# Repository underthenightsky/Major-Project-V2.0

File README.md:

# Major Project V2.0
Research Paper to compare various models on a STM32F401CCU6 and design a PCB for pracitcal applications

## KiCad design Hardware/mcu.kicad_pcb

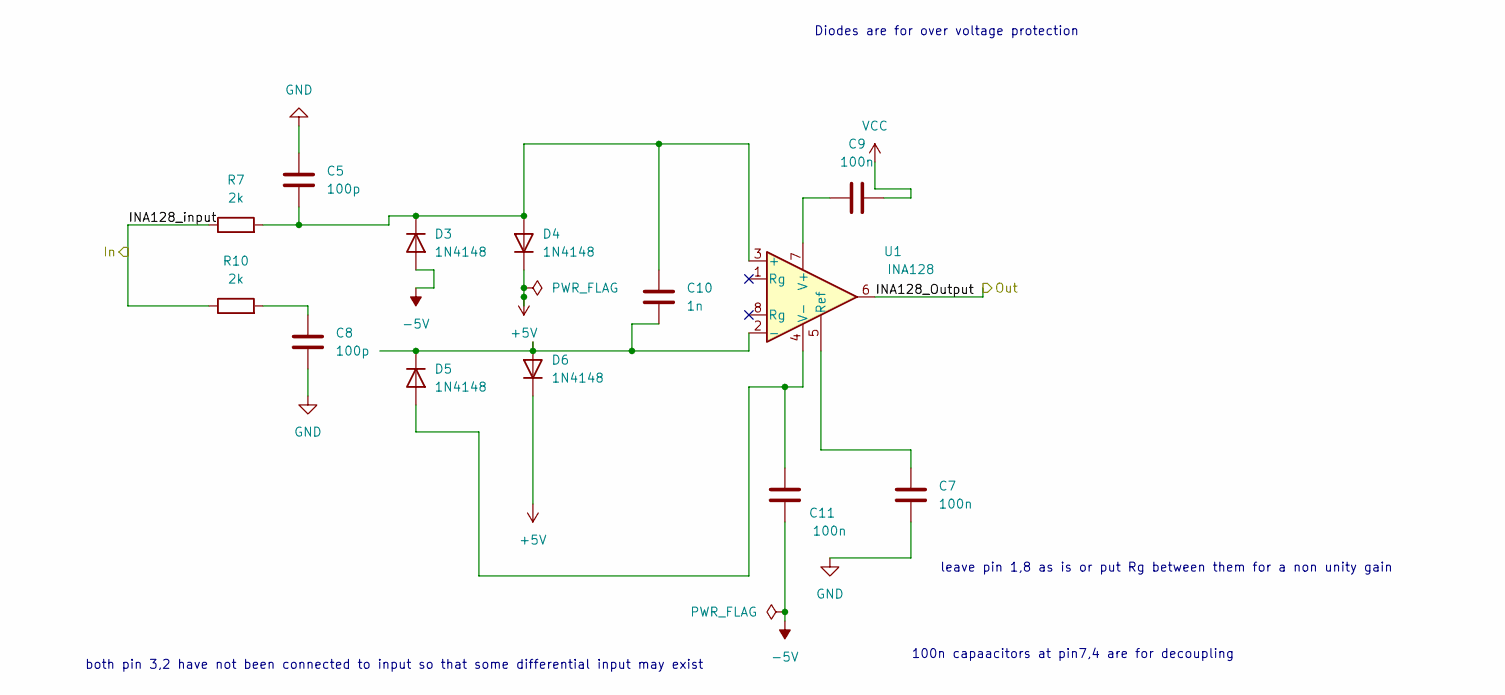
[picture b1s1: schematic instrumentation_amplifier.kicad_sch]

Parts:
C5, C8: 100p; C_0805_2012Metric
C7, C9, C11: 100n; C_01005_0402Metric
C10: 1n; C_0805_2012Metric
D3, D4, D5, D6: 1N4148; D_DO-35_SOD27_P7.62mm_Horizontal
R7, R10: 2k; R_0805_2012Metric
U1: INA128; SOIC-8_3.9x4.9mm_P1.27mm

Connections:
+5V: D4.1 (K), D6.1 (K); also elsewhere on the board
-5V: C11.2, D3.2 (A)
/instrumentation_amplifier/INA128_Output: U1.6; also elsewhere on the board
/instrumentation_amplifier/INA128_input: R7.1, R10.1; also elsewhere on the board
GND: C5.2, C7.2, C8.2; also elsewhere on the board
unnamed: C8.1, R10.2
unnamed: C5.1, C10.1, D3.1 (K), D4.2 (A), R7.2, U1.3 (+)
unnamed: C11.1, D5.2 (A), U1.4 (V-)
unnamed: C10.2, D5.1 (K), D6.2 (A), U1.2 (-)
unnamed: C7.1, U1.5 (Ref)
unnamed: C9.1, U1.7 (V+)
VCC: C9.2; also elsewhere on the board

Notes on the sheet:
100n capaacitors at pin7,4 are for decoupling
Diodes are for over voltage protection
both pin 3,2 have not been connected to input so that some differential input may exist
leave pin 1,8 as is or put Rg between them for a non unity gain

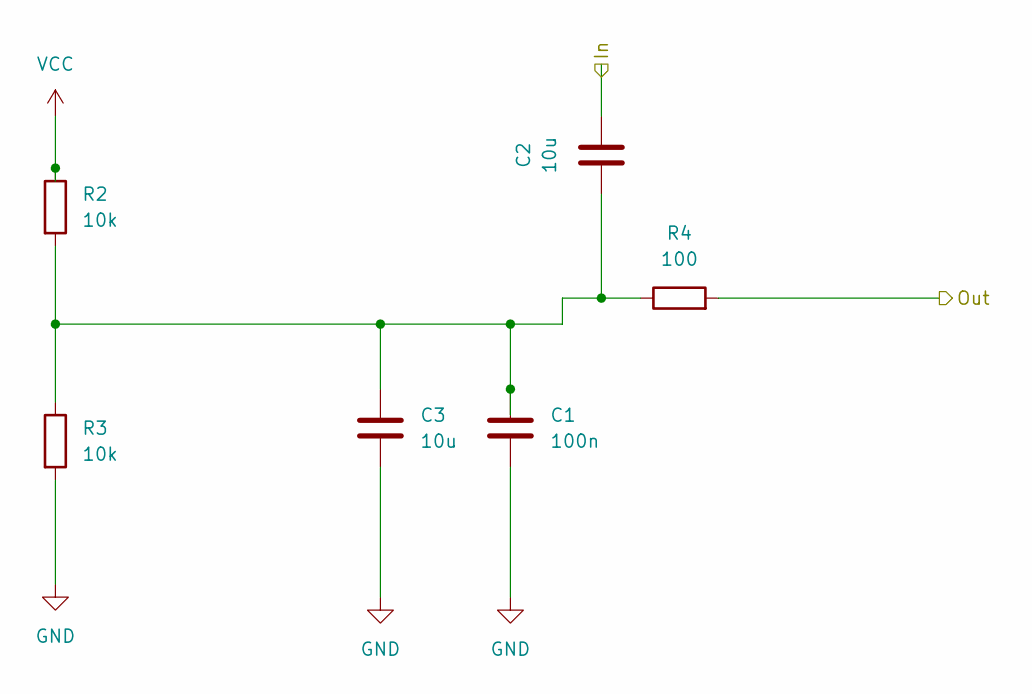
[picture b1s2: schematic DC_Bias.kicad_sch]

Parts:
C1: 100n; C_0805_2012Metric
C2: 10u; C_0805_2012Metric
C3: 10u; CP_Elec_6.3x5.4
R2, R3: 10k; R_0805_2012Metric
R4: 100; R_0805_2012Metric

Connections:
/DC_Bias/In: C2.2; also elsewhere on the board
/DC_Bias/Out: R4.2; also elsewhere on the board
GND: C1.2, C3.2, R3.2; also elsewhere on the board
unnamed: C1.1, C2.1, C3.1, R2.2, R3.1, R4.1
VCC: R2.1; also elsewhere on the board

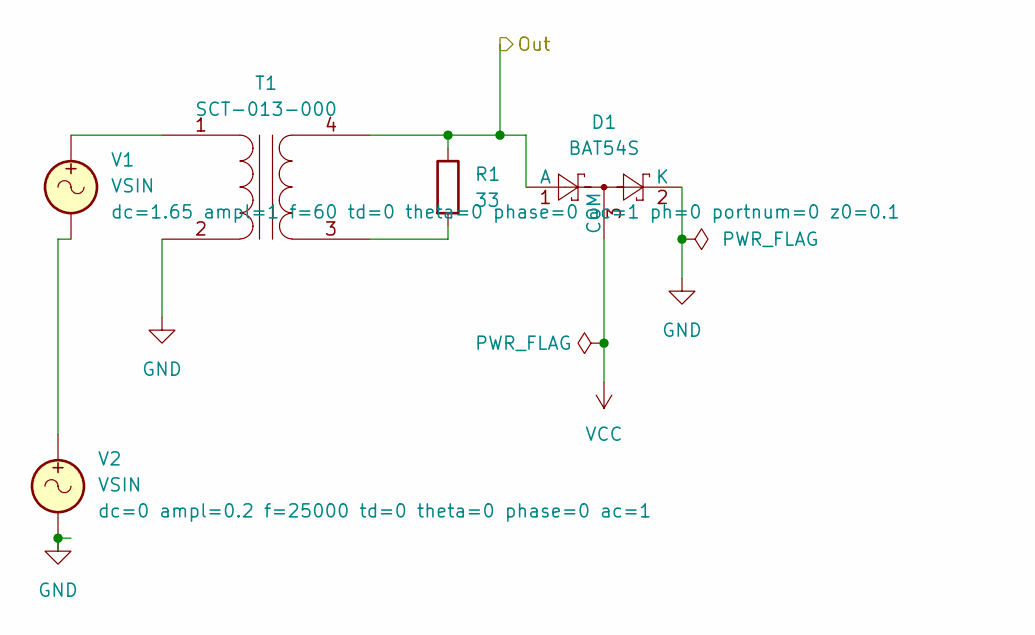
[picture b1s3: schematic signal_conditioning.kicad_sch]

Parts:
D1: BAT54S; SOT-23
R1: 33; R_0805_2012Metric
T1: SCT-013-000; TerminalBlock_MaiXu_MX126-5.0-04P_1x04_P5.00mm
V1, V2: VSIN

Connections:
/DC_Bias/In: D1.1 (A), R1.1, T1.4 (SB); also elsewhere on the board
GND: D1.2 (K), T1.2 (AB), V2.2; also elsewhere on the board
unnamed: T1.1 (AA), V1.1
unnamed: R1.2, T1.3 (SA)
unnamed: V1.2, V2.1
VCC: D1.3 (COM); also elsewhere on the board

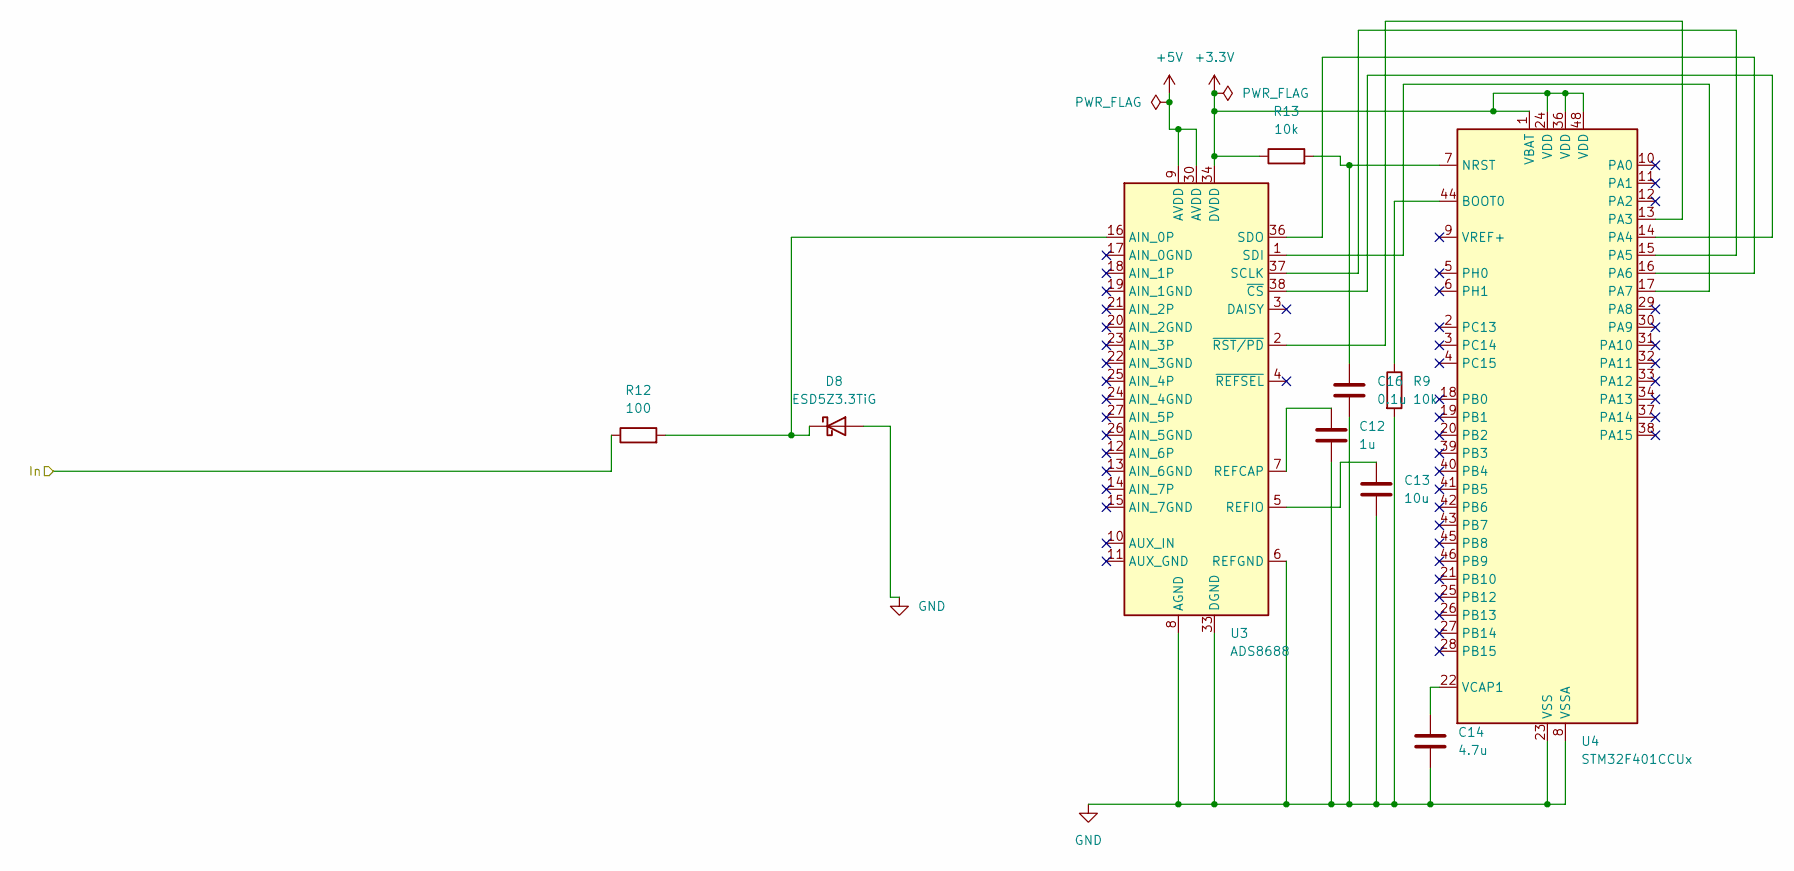
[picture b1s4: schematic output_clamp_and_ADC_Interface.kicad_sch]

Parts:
C12: 1u; C_0805_2012Metric
C13: 10u; C_0805_2012Metric
C14: 4.7u; C_0805_2012Metric
C16: 0.1u; C_0805_2012Metric
D8: ESD5Z3.3TiG; D_SOD-523
R9, R13: 10k; R_0805_2012Metric
R12: 100; R_0603_1608Metric
U3: ADS8688; TSSOP-38_4.4x9.7mm_P0.5mm
U4: STM32F401CCUx; QFN-48-1EP_7x7mm_P0.5mm_EP5.6x5.6mm

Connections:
+3.3V: R13.1, U3.34 (DVDD), U4.1 (VBAT), U4.24 (VDD), U4.36 (VDD), U4.48 (VDD)
+5V: U3.9 (AVDD), U3.30 (AVDD); also elsewhere on the board
/instrumentation_amplifier/INA128_Output: R12.1; also elsewhere on the board
GND: C12.2, C13.2, C14.2, C16.2, D8.2 (A), R9.2, U3.6 (REFGND), U3.8 (AGND), U3.28 (AGND), U3.29 (AGND), U3.31 (AGND), U3.32 (AGND), U3.33 (DGND), U4.8 (VSSA), U4.23 (VSS), U4.35 (VSS), U4.47 (VSS), U4.49 (VSS); also elsewhere on the board
unnamed: D8.1 (K), R12.2, U3.16 (AIN_0P)
unnamed: C12.1, U3.7 (REFCAP)
unnamed: C13.1, U3.5 (REFIO)
unnamed: U3.37 (SCLK), U4.15 (PA5)
unnamed: U3.1 (SDI), U4.17 (PA7)
unnamed: U3.36 (SDO), U4.16 (PA6)
unnamed: U3.38 (~CS), U4.14 (PA4)
unnamed: U3.2 (~RST/PD), U4.13 (PA3)
unnamed: R9.1, U4.44 (BOOT0)
unnamed: C16.1, R13.2, U4.7 (NRST)
unnamed: C14.1, U4.22 (VCAP1)

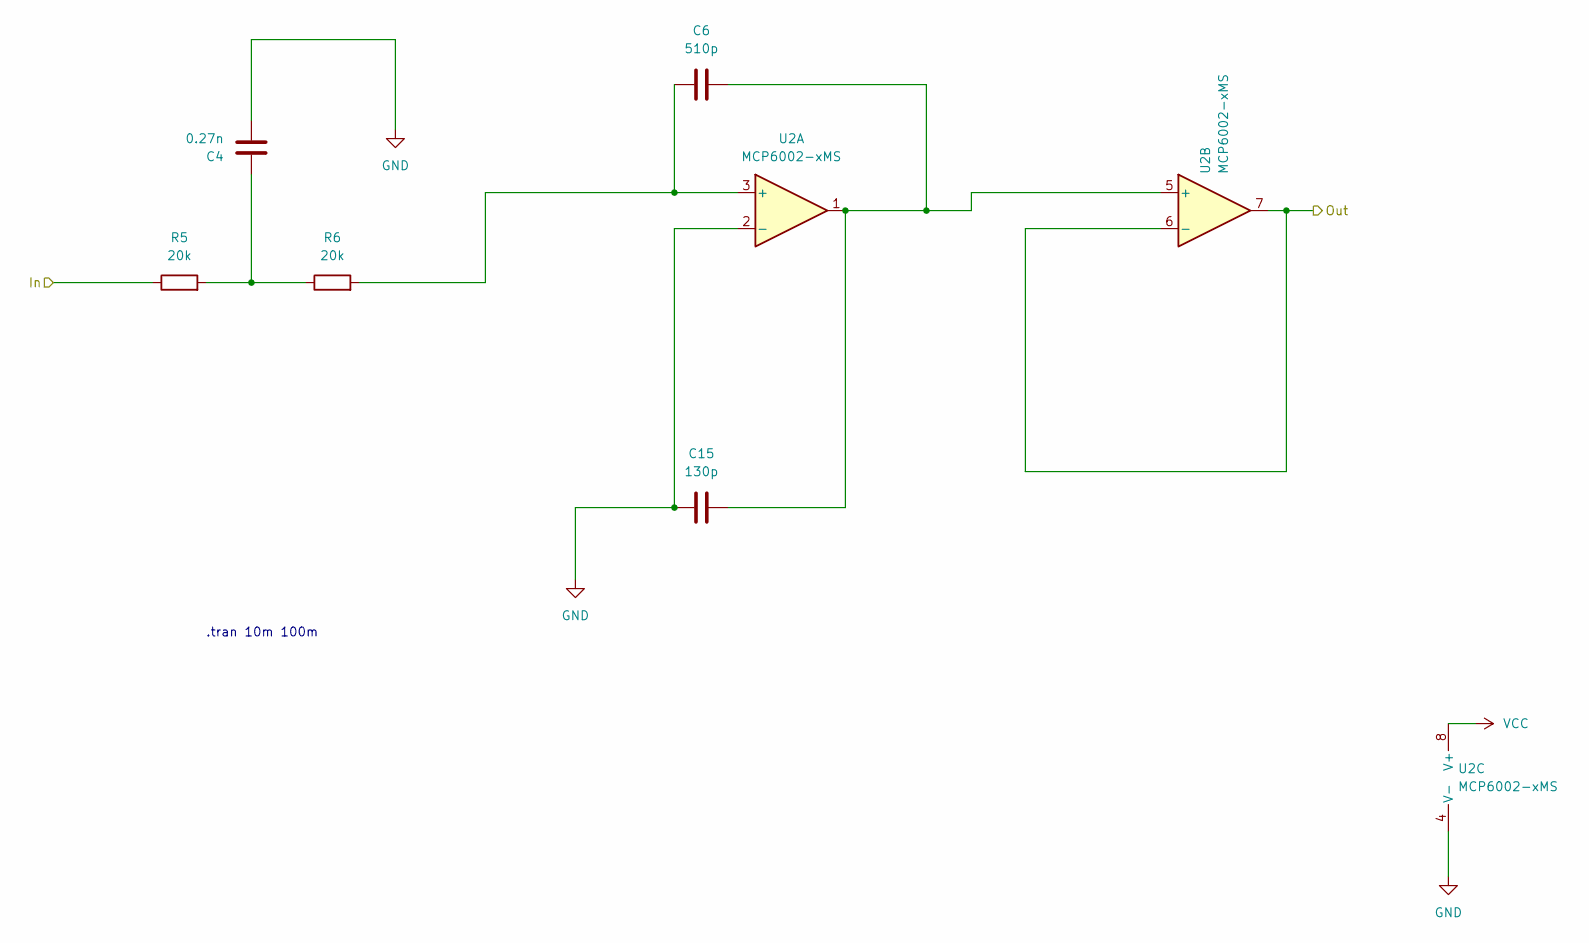
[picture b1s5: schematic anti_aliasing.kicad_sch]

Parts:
C4: 0.27n; C_0805_2012Metric
C6: 510p; C_0805_2012Metric
C15: 130p; C_0805_2012Metric
R5, R6: 20k; R_0805_2012Metric
U2: MCP6002-xMS; MSOP-8_3x3mm_P0.65mm

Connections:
/DC_Bias/Out: R5.1; also elsewhere on the board
/instrumentation_amplifier/INA128_input: U2.6 (-), U2.7; also elsewhere on the board
GND: C4.2, C15.1, U2.2 (-), U2.4 (V-); also elsewhere on the board
unnamed: C4.1, R5.2, R6.1
unnamed: C6.2, R6.2, U2.3 (+)
unnamed: C6.1, C15.2, U2.1, U2.5 (+)
VCC: U2.8 (V+); also elsewhere on the board

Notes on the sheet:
.tran 10m 100m

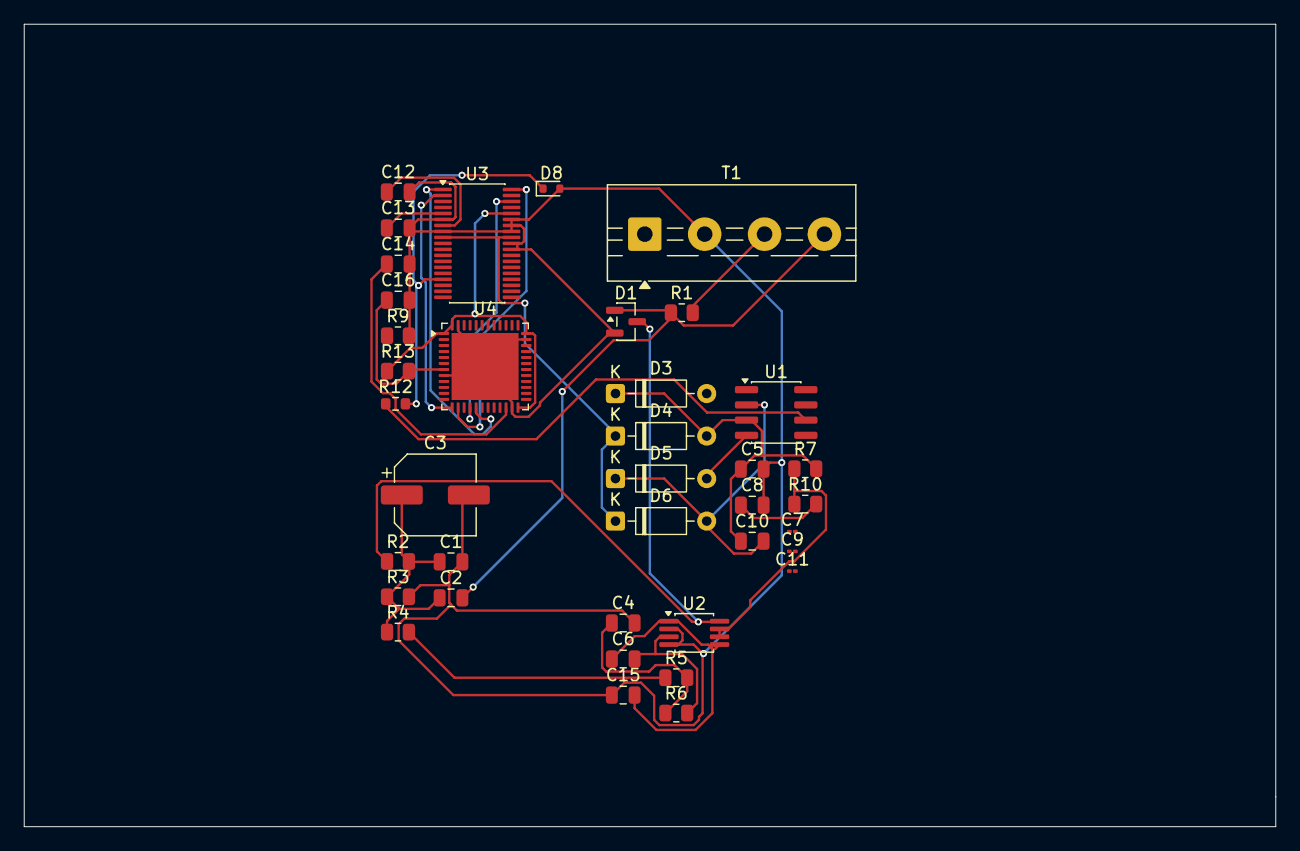
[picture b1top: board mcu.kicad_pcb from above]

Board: 4 copper layers, 104.5 x 67.0 mm, 38 parts (0 on the bottom side), 31 nets.

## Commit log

2026-06-23 added better folders
2026-06-30 completed hardware
